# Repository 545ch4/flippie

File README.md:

# flippie

## Basic idea and some background

Usual story: no money, lots of deadlines, unsustainable promises, social responsibility, no time at all, but the unique opportunity to get an additional time-sink. Yeah. Seconds later, I got two huge flip-dot displays I couldn't even carry myself and a lot of single modules. Soon (measured in seasons) it became obvious, that reverse engineering the RS485 based IBIS bus would not make me very happy in the long run. So I decided to throw away the original controller board and drive the flip-dot modules myself. **The goal would be a non intrusive board to directly connect any BROSE display (or array of the same) through the proprietary 60-pin connector...**  So, this is the story of that effort...

### Flip-dot display in general

A flip-dot display consists of a grid of small magnet embedded discs that are black on one side and a bright color on the other (typically white or yellow). The discs are attached to an axle with separate solenoids arranged at the ends or side. By pulsing the solenoid coil with the appropriate electrical polarity, the permanent magnet on the discs align itself with the magnetic field and thus turning (flipping) the disc.

The matrix schematic arranged on a two-dimensional area is shown below.

### BROSE flip-dot

Most BROSE flip-dots are equipped with an [origial FP2800A (or clone)](https://reaktor23.org/_media/projects/flipdot/fp2800-datasheet.pdf) decoder driver as column-selector. It drives one line addressed by 5-bits (A0, A1, A2, B1 and B2) in the direction of D (GND or +VS).  Based on the truth-table, 28 independent column-lines can be driven.

The address lines (ADDR1..ADDR8) are compared to an DIP-switch on each module using a 74HCT688. The output of that comparison drives the ENABLE pin of the FP2800A (through a discrete inverter).

All data and address lines are at 24V logic level. The VS line should be current limited to 350-400 mA, because the coils and/or the FP2800A may blow at higher current.

I did a reverse engineering of the 24V logic at the BROSE display just for illustration. Download as [PDF](https://github.com/545ch4/flippie/raw/master/board/docs/brose_24v_logic.pdf) or [Eagle SCH](https://github.com/545ch4/flippie/raw/master/board/docs/brose_24v_logic.sch).

### BROSE 60-pin connector

## flippie board

The board was designed to drive every serial assembly of modules or single ones non-intrusively - without soldering or modifying the module(s) - simply by connection the proprietary 60-pin BROSE connector. The main MCU [ESP8266](https://espressif.com/en/products/hardware/esp8266ex/overview) is mounted on a USB-interfaced USB-to-Serial converter for convenient programming and WiFi on board. Please see [wemos D1 mini](https://www.wemos.cc/product/d1-mini.html) documentation. Usually you need some driver for the converter to be detected as serial port depending on your OS. The wemos D1 mini comes with a Jiangsu Qinheng CH340/CH341/CH34X or Silicon Labs CP210x chip.

### Block diagram

### Schematics

Since this is my first PCB, the schematic may be slightly unusual. But it works... Suggestions are very welcome. Get the [Eagle SCH file](https://github.com/545ch4/flippie/raw/master/board/flippie.sch) or see the [PDF file](https://github.com/545ch4/flippie/raw/master/board/flippie_schematics.pdf).

### Layout

Download the [Eagle BRD](https://github.com/545ch4/flippie/board/flippie.brd) file and/or the generated [GERBER files as ZIP archive](https://github.com/545ch4/flippie/raw/master/board/gerber.zip). All design rules are taken from [SparkFuns Extended Gerber Format](https://github.com/sparkfun/SparkFun_Eagle_Settings/blob/master/cam/sfe-gerb274x-withGBP.cam).

### BOM

| Part | Value      | Device        | Package       | Description |
|------|------------|---------------|---------------|-------------|
| Part Value | Device | Package | Description |
| C1 | 100uF/50V | CPOL-EU_E | PANASONIC_E | Polarized capacitor, 50V |
| C2 | 10uF/50V | C-EU_C1206 | C1206 | X7R Ceramic Capacitor, 50V |
| C3 | 1uF/50V | C-EU_C1206 | C1206 | X7R Ceramic Capacitor, 50V |
| IC1 | 74HCT245DW | 74HCT245DW | SO20W | Octal BUS TRANSCEIVER, 3-state, TTL/CMOS |
| IC2 | FPF2702MX | FPF2700 | SO8N | AccuPower 0.4~2 A Adjustable Over-Current Protection Load Switch |
| IC3 | SN74AHC595D | SN74AHC595D | SO16N | 8 bit Shift registers |
| ... | ... | ... | ... | ... |
| IC9 | SN74AHC595D | SN74AHC595D | SO16N | 8 bit Shift registers |
| IC10 | TD62783AFG | UDN2981LW | SO18W | PMOS Darlington transistor array |
| IC11 | TD62783AFG | UDN2981LW | SO18W | PMOS Darlington transistor array |
| IC12 | TD62783AFG | UDN2981LW | SO18W | PMOS Darlington transistor array |
| IC13 | ULN2803A | ULN2803ADW | SO18W | NMOS Darlington transistor array |
| ... | ... | ... | ... | ... |
| IC17 | ULN2803A | ULN2803ADW | SO18W | NMOS Darlington transistor array |
| JP1 | 3V3 | JP1E | JP1 | 3.3V Rail Jumper |
| JP2 | 24V | JP1E | JP1 | 24V Rail Jumper |
| JP3 | 5V | JP1E | JP1 | 5V(VCC) Rail Jumper |
| JP4 | VS | JP1E | JP1 | 24V(VS) Jumper |
| LED1 C (red) | LED_SMT1206 | 1206 | LED |
| LED2 B (yellow) | LED_SMT1206 | 1206 | LED |
| LED3 A (green) | LED_SMT1206 | 1206 | LED |
| MCU1 | WEMOS D1 mini | WEMOS D1 mini | WEMOS D1 mini MCU |
| PAD1 (24V) | 2,15/1,0 | 2,15/1,0 | THROUGH-HOLE PAD |
| PAD2 (VS) | 2,15/1,0 | 2,15/1,0 | THROUGH-HOLE PAD |
| R1 | 680K | R-EU_R1206 | R1206 | Current limiter Resistor R_set |
| R2 | 100K | R-EU_R1206 | R1206 | Resistor |
| R3 | 10K | R-EU_R1206 | R1206 | Resistor |
| R4 | 10K | R-EU_R1206 | R1206 | Resistor |
| R5 | 10K | R-EU_R1206 | R1206 | Resistor |
| R6 | 220 | R-EU_R1206 | R1206 | Resistor |
| R7 | 220 | R-EU_R1206 | R1206 | Resistor |
| R8 | 220 | R-EU_R1206 | R1206 | Resistor |
| X1 | 3V3 | JST-XH-02 | JST-XH-02-PACKAGE-LONG-PAD | JST XH Connector 2 Pin |
| X2 | 5V | JST-XH-02 | JST-XH-02-PACKAGE-LONG-PAD | JST XH Connector 2 Pin |
| X3 | 24V | JST-XH-02 | JST-XH-02-PACKAGE-LONG-PAD | JST XH Connector 2 Pin |
| X4 | ~EN_PWR | JST-XH-02 | JST-XH-02-PACKAGE-LONG-PAD | JST XH Connector 2 Pin |
| X5 | BROSE-60-POL | 057-060-1 | 057-060-1 | 60-pol. BROSE CONNECTOR |

### Soldering notes

You can override the whole current limit circuit by shorting/bridging PAD1 (24V) and PAD2 (VS). If you decided to do so, you don't need to populate C1, C2, C3, R1, R2 and IC2.

> **Close JP1 (3V3) and JP2 (24V) but not JP4 (VS) yet.**

## Code

### Prerequisites

Since building and maintaining an ESP8266 toolchain using the [Arduino ESP8266 Framework](https://github.com/ESP8266/Arduino) can be rather frustrating, I decided to use [PlatformIO](http://platformio.org/platformio-ide) with this project.

1. [Download PlatformIO](http://platformio.org/platformio-ide) and install
2. Launch and follow on-screen instructions (install Python-2.7 if necessary)
3. [Install Clang/LLVM](http://docs.platformio.org/en/stable/ide/atom.html#ide-atom-installation-clang)
4. Ensure `platformio-ide` and `platformio-ide-terminal` are enabled (*"Settings > Packages"*)

### Open the project

Download or clone this repository. Open the directory `./code/server` using *"Open project"* at PlatformIO IDE.

### Necessary adoptions

Review you flip-dot addresses: **ADDR8 (8 on the DIP-switch) must be in ON state. We are emulating an overall-enable-pin with that one. Further, the addresses are inverted. So, address 0x01 matches the DIP-switch configuration 1-OFF, 2-ON, ..., 7-ON an 8-ON.**

Before you compile and upload your custom firmware to the ESP8266, there are some values specific to your setup/environment to be defined.
**Flip-dot configuration at `code/server/flippie_device.cpp`:**
```c++
// TODO: How many modules does your display consists of?
const unsigned int num_modules = 4;
config.num_modules = num_modules;
// TODO: What are the addresses (as decimal) of the modules? (see DIP-switches at each module)
config.addresses = new unsigned int[num_modules]{1, 2, 4, 8};
// TODO: How many rows does your display have? (equal over all modules)
config.num_rows = 18;
// TODO: How many columns does each module of your display have? (same order as the addresses)
config.num_columns = new unsigned int[num_modules]{28, 28, 28, 21};
// TODO: Should LED C toggle on each shift-register firing?
config.led_mode = LED_MODE_FLASHING;
```

**WiFi configuration at `code/server/main.cpp`:**
```c++
// TODO: What's the SSID of your WiFi?
const char* ssid = "SSID";
// TODO: What's the PASSWORD of your WiFi?
const char* password = "PASSWORD";
// TODO: If you don't want to use DHCP, provide a static IP (uncomment the following lines). Otherwise leave this commented.
// IPAddress ip(192, 168, 1, 23);
// IPAddress gateway(192, 168, 1, 1);
// IPAddress subnet(255, 255, 255, 0);
// WiFi.config(ip, gateway, subnet);
```

### Compile and upload firmware

> **Please disconnect the power supply of your flippie board or remove the jumper JP1 und JP3 before connecting your computer to the USB port of the ESP8266 (if mounted at the flippie board already).**

Navigate to *"PlatformIO > Build"* to compile this project and create the firmware for uploading to the ESP8266. Use *"PlatformIO > Upload"* to upload your firmware using the USB connection.

### Test

Disconnect flippie from USB or press the reset button of the wemos D1 mini board. Plug the wemos D1 mini to flippie, ensure to close JP1 (3V3), JP2 (24V) and JP3 (5V) **but not JP4 (VS) yet**. All three LEDs should flash three times. If not, the shift-register(s) doesn't seems to work properly... [So, check your soldering.](http://www.infidigm.net/articles/solder/)

If the LEDs were flashing during boot-up, don't yet connect the display itself. Point your browser to `http://<flippie IP>/`. That's the web-interface of flippie. You've done well so far.

Since you don't want to damage your display, we will try to set and reset some dots in a dry run first (**AKA: don't connect your flipdot display yet**):

0. Make sure your display is **not** connected (X5), jumper JP4 (VS) is **closed/shorted** and all three power rails (3V3, 5V and 24V) are enabled through JP1, JP2, JP3.
1. Head to "Low Level" in at flippies web-interface.
2. Fill the form for
   1. Select the address of one of your panels (e.g. 1)
   2. Select a column we are going to use (Column, e.g. 10)
   3. Set "Row SET" to '0' (first row)
   4. Leave "Row RST" undefined
   5. Set the direction D to "1" (D=1 when setting (ROW_SET) and D=0 when reseting (ROW_RST) a pixel)
4. Press "Fire shift-register (PERSISTENT)"
   1. IC12 pin 11 should drive +24V (first row rail, same as pin 1 at X5)
   2. IC16 pin 18 should go to GND (our simulated ENABLE signal, same as pin 60 at X5)
5. Press "Fire shift-register (ENABLE)" to quit "PERSISTENT" mode.

Repeat the test with flipdot display connected (X5):

0. Make sure your display **is** connected (X5), jumper JP4 (VS) is **open** and all three power rails (3V3, 5V and 24V) are enabled through JP1, JP2, JP3.
1. Head to "Low Level" in at flippies web-interface.
2. Fill the form for
   1. Select the address of one of your panels (e.g. 1)
   2. Select a column we are going to use (Column, e.g. 10)
   3. Set "Row SET" to '0' (first row)
   4. Leave "Row RST" undefined
   5. Set the direction D to "1" (D=1 when setting (ROW_SET) and D=0 when reseting (ROW_RST) a pixel)
4. Press "Fire shift-register (PERSISTENT)"
5. Now take a jumper and use it to **shortly bypass** (close shortly and then open again) JP4 (VS): **The dot should flip!**
6. Repeat the procedure with "Row SET" undefined, "Row RST" set to '0' and D set to '0'. **The dot should flip back!**
5. Press "Fire shift-register (ENABLE)" to quit "PERSISTENT" mode.

**Well done!** You're ready to use your flippie! [Simply head over to "Paint" and draw something.](#paint)

### Firmware API documentation

Flippie is basically a simple web server at port 80 serving the following access points:

**`/ui` – UI pages**  
A simple index page with browser UI controlling the flip-dot. All javascript and stylesheets are loaded from an external CDN, not from the ESP8266 itself. So, you need to be connected to the internet... (Yes, it's an TODO.)

The UI does have a nice drawing pane, where every pixel can be set/reset like painting using a HTML5 canvas.

**`/dots` – A receiver of base64 encoded dots vector**  
This method reads the content of HTTP (POST/GET) variable `dots` which is a base64 encoded string. This string is build of 32-bit wide integers (four bytes) where each bit (0-31) represents the state of one column. Those integers are ordered by rows and then modules:
```
[row 1 column 1-32* module 1], [row 1 column 1-32* module 2], ..., [row 1 column 1-32* module M], [row 2 column 1-32* module 1], [row 2 column 1-32* module 2], ..., ..., [row R column 1-32* module M]
```
\* max, could be less, ignoring unnecessary bits. Each integer is packed as four 8-bit characters in LSB order.

**`/flippie` – Directly alter the shift register at flippie (possibly dangerous)**

Low level access to flippie. Set using HTTP variables (POST) and retrieve values as JSON using GET. POST request will return JSON `true`.

| HTTP verb | Variable       | Value           | Description                   |
|-----------|----------------|---------------- |-------------------------------|
| GET/POST  | led_X          | 0, 1            | Get/Set the state of LED X (A, B, C) |
| GET/POST  | address        | 0 - 127         | Get/Set the module address |
| GET/POST  | column         | 0 - 27          | Get/Set the active column |
| GET/POST  | d              | 0, 1            | Set FP2800A D pin (1 = selected column set to GND, 0 = selected column set to +VS) |
| GET/POST  | row_set        | 0 - 19          | Set the selected row to +VS |
| GET/POST  | row_rst        | 0 - 19          | Set the selected row to GND |
| GET/POST  | enable         | 0, 1            | Set enable if 1 (dangerous) |
| POST      | clear          | 0, 1            | Clear shift-register if 1 |
| GET       | shiftregister  | String          | Get contents of the shift-register as sequence of zeros and ones. |
| POST      | task           | clear           | Clear the whole display |
| POST      | task           | fill            | Fill the whole display (set all dots) |
| POST      | task           | inverse         | Inverse the whole display |
| POST      | task           | magnetize       | Magnetize the whole display |

Basic mechanism to set a dot (column 2, row 3) at module 0 with address 0x01 (DIP switch 0-1-1-1-1-1-1-0) using raw HTTP:
```shell
$ telnet <flippie IP> 80
> POST /flippie HTTP/1.0
> Content-Length: 41
>
> address=1&column=1&row_set=2&d=1&enable=1
```

**`/pixel` – Set individual pixels**

| HTTP Variable          | Description |
|------------------------|-------------|
| r(0-31)                | Row |
| m(0-128)               | Module |
| c(0-31)                | Column |
| state(0/1)             | Set of reset the pixel |

A GET request will reveal the state of an pixel and a POST will set the state.

## Demo ruby client

There's a simple demo-like ruby implementation to write text at a given display. To use it, please head yourself to the directory `./client/` and initialize the ruby environment with:
```shell
gem install bundler
bundle install
```

Adjust flippies credentials in `cli.rb`:
```ruby
# initialize new flippie client
fc = FlippieClient.new(
   '192.168.1.23',     # IP address of your flippie board
   18,                  # number of rows of your flip-dot display
   [21],                # number of columns per module (usually some 28ers an one 21er)
   false                # debug => true
)
```

You are now ready to send messages/text to your flippie board using the ruby tool. Example:
```shell
./cli.rb YES
```
You should see an visual response of "YES" on your command line as well as the same text on your flip-dot display, obviously. See the source for further options.

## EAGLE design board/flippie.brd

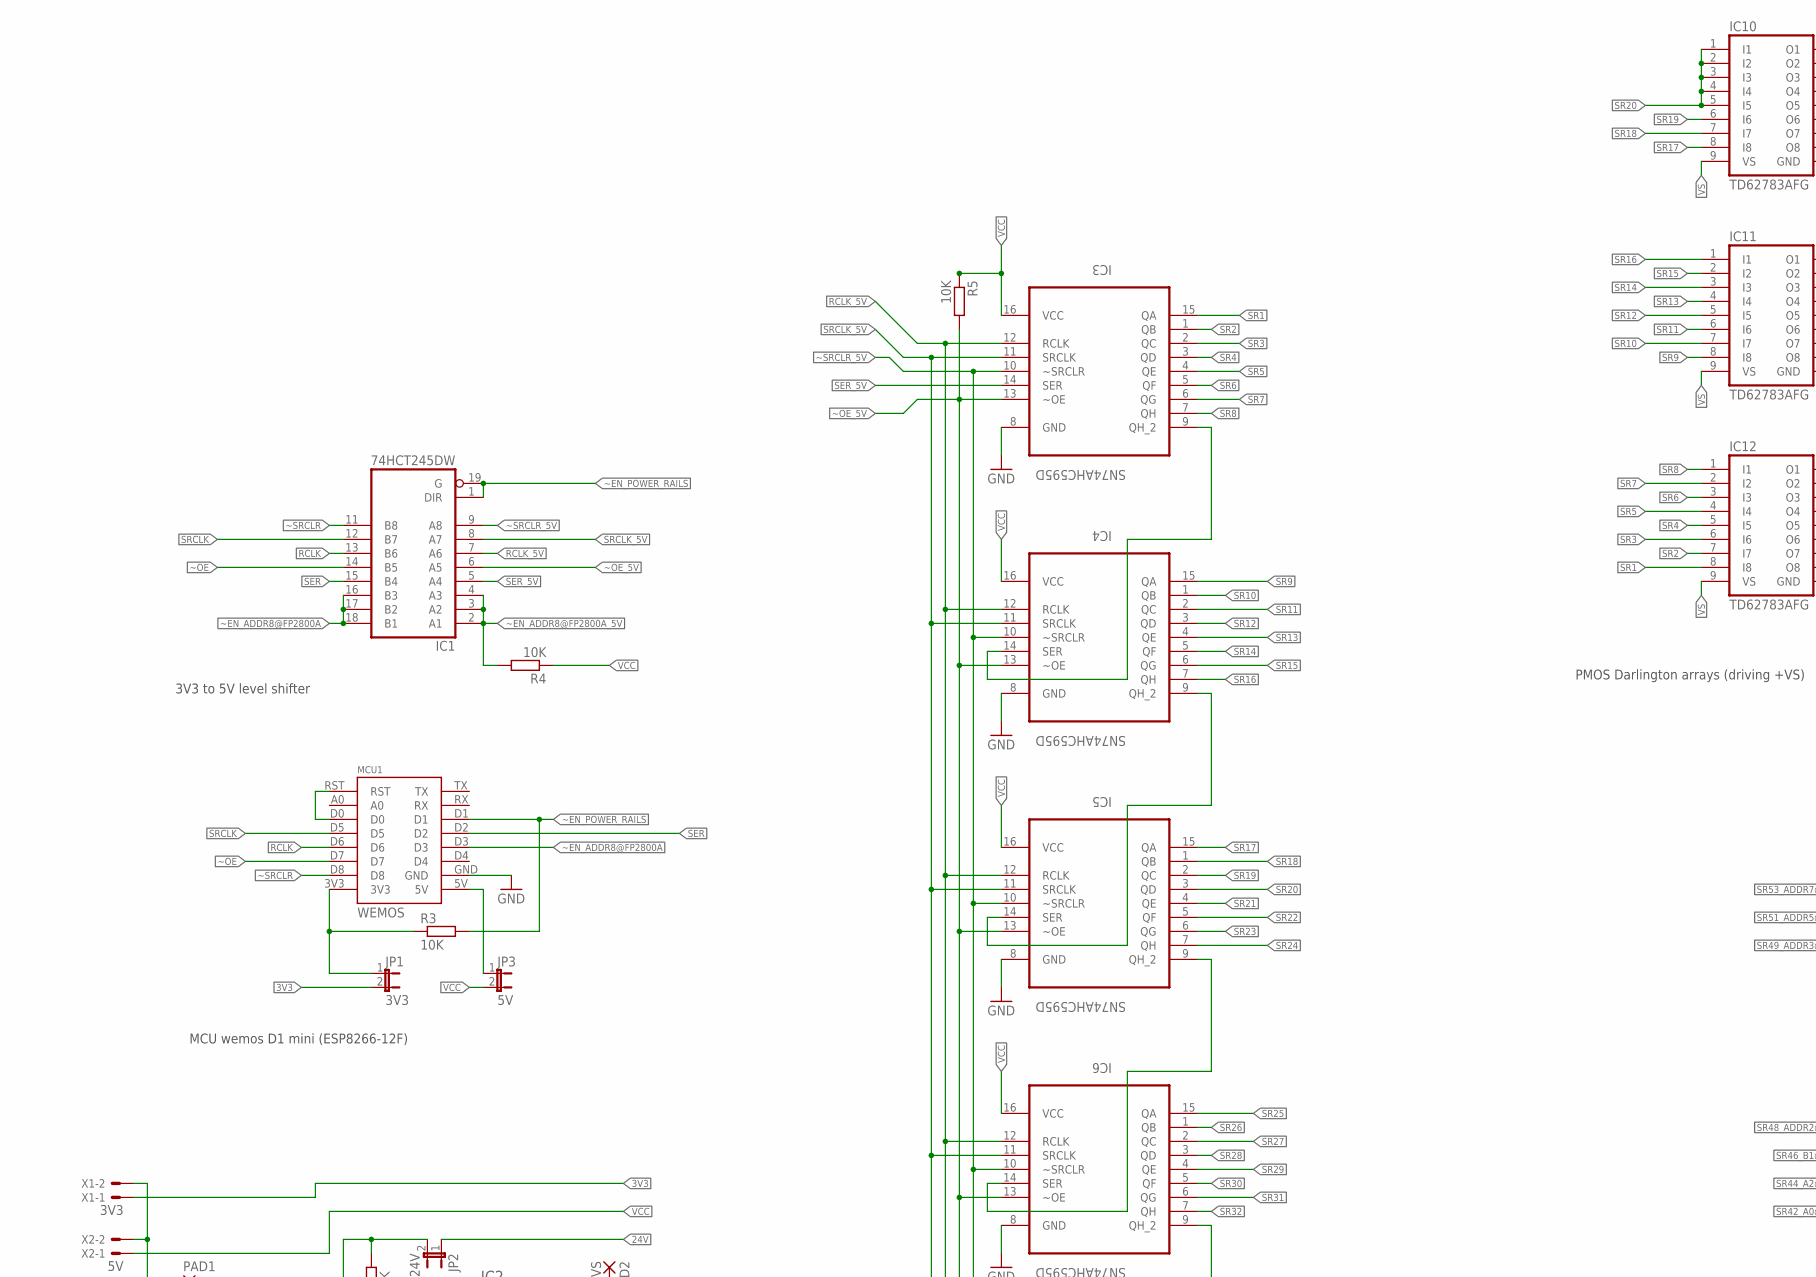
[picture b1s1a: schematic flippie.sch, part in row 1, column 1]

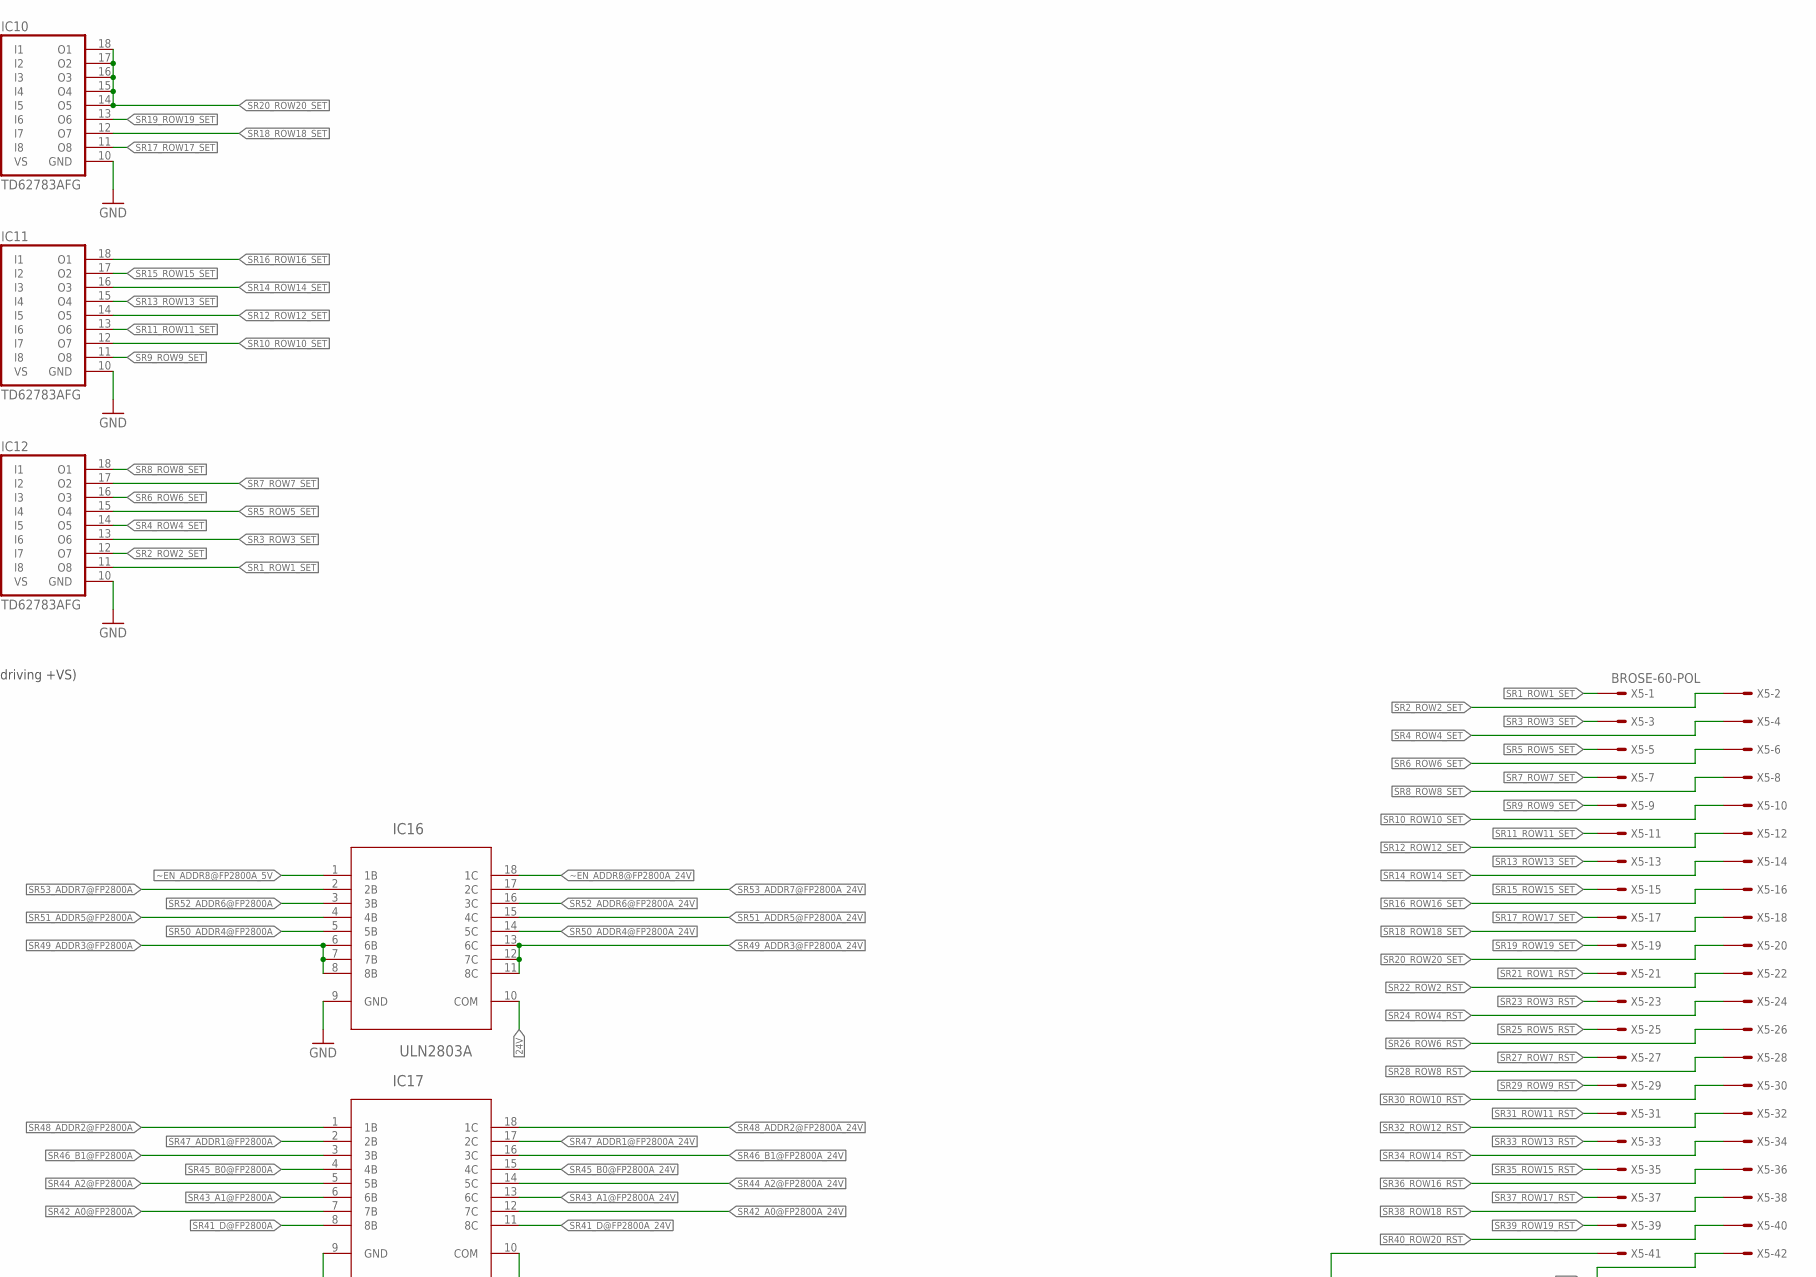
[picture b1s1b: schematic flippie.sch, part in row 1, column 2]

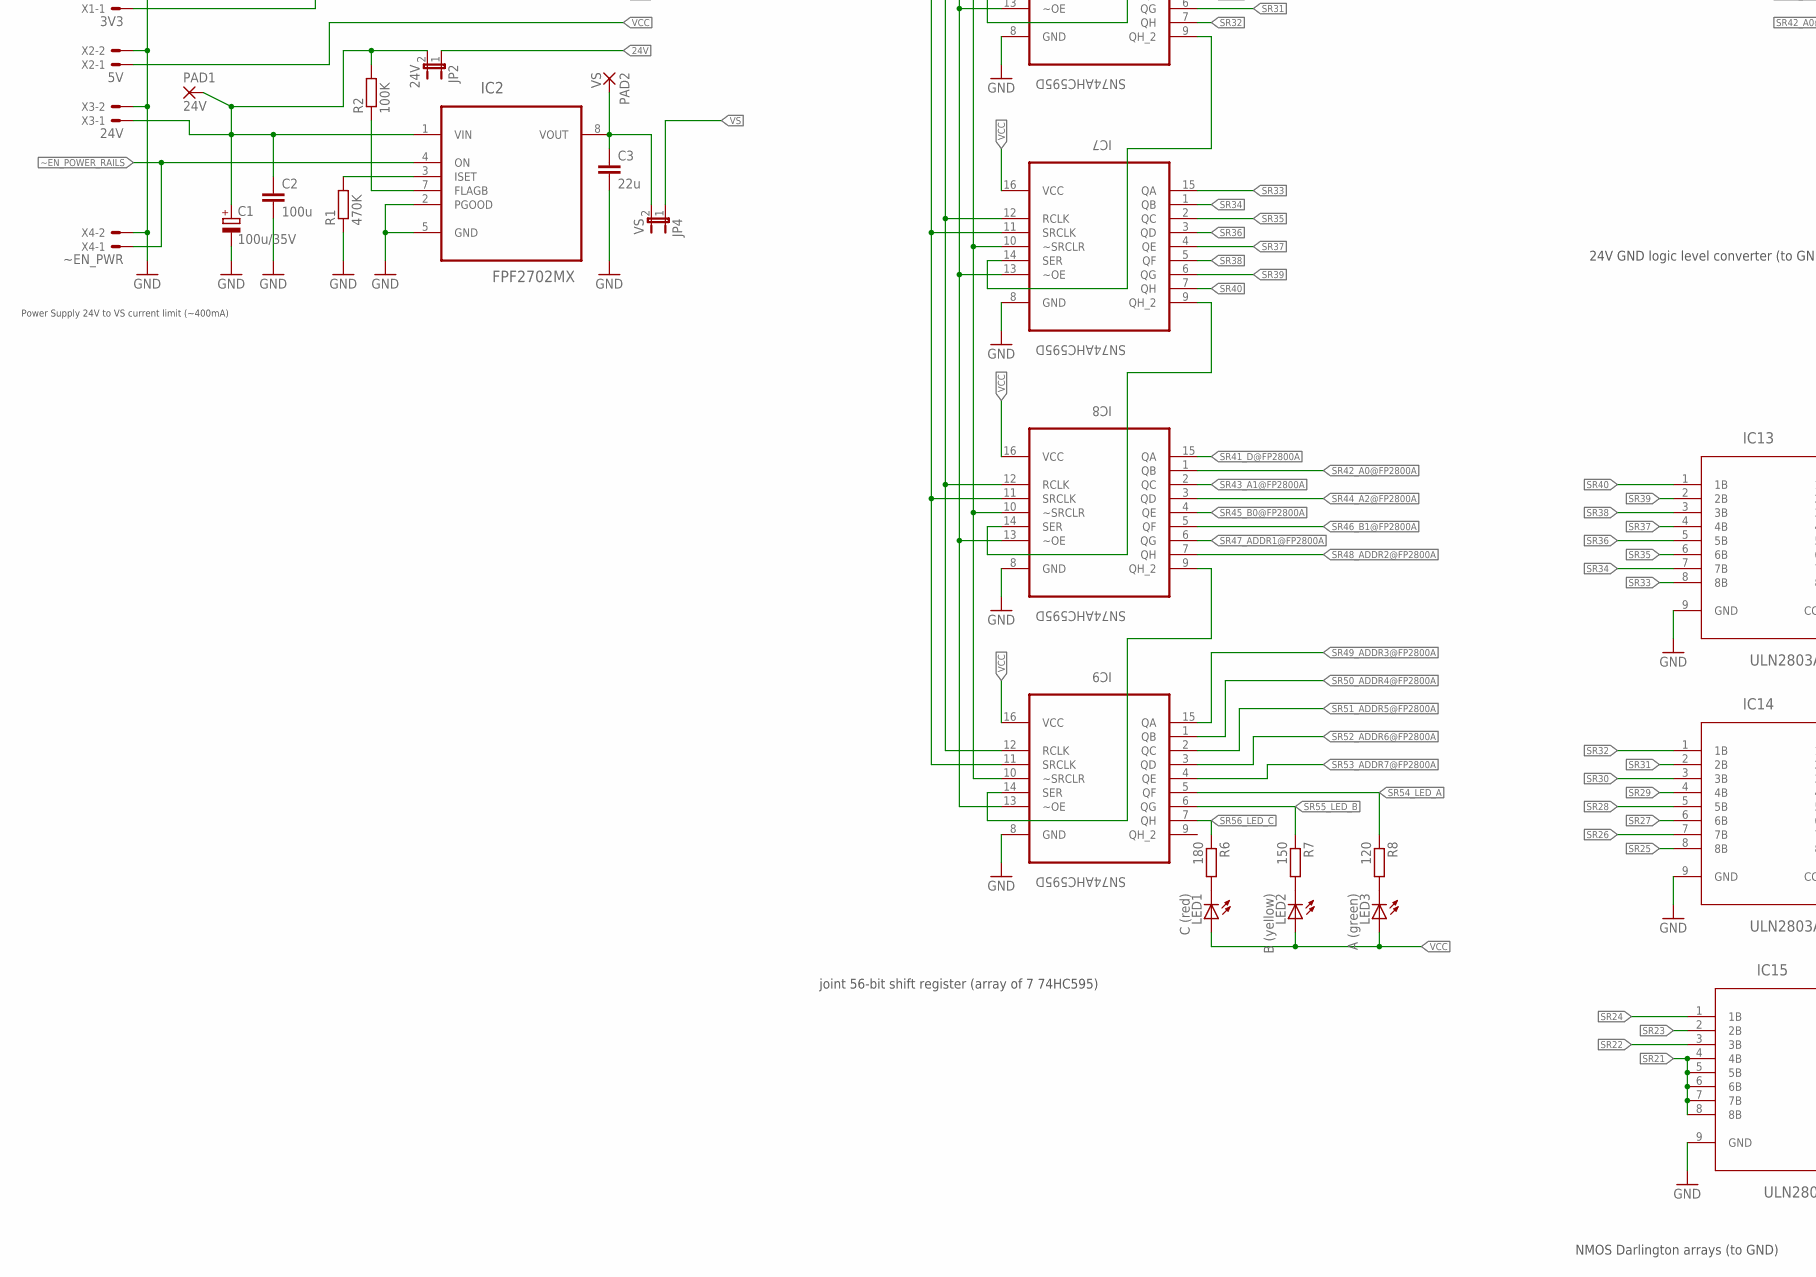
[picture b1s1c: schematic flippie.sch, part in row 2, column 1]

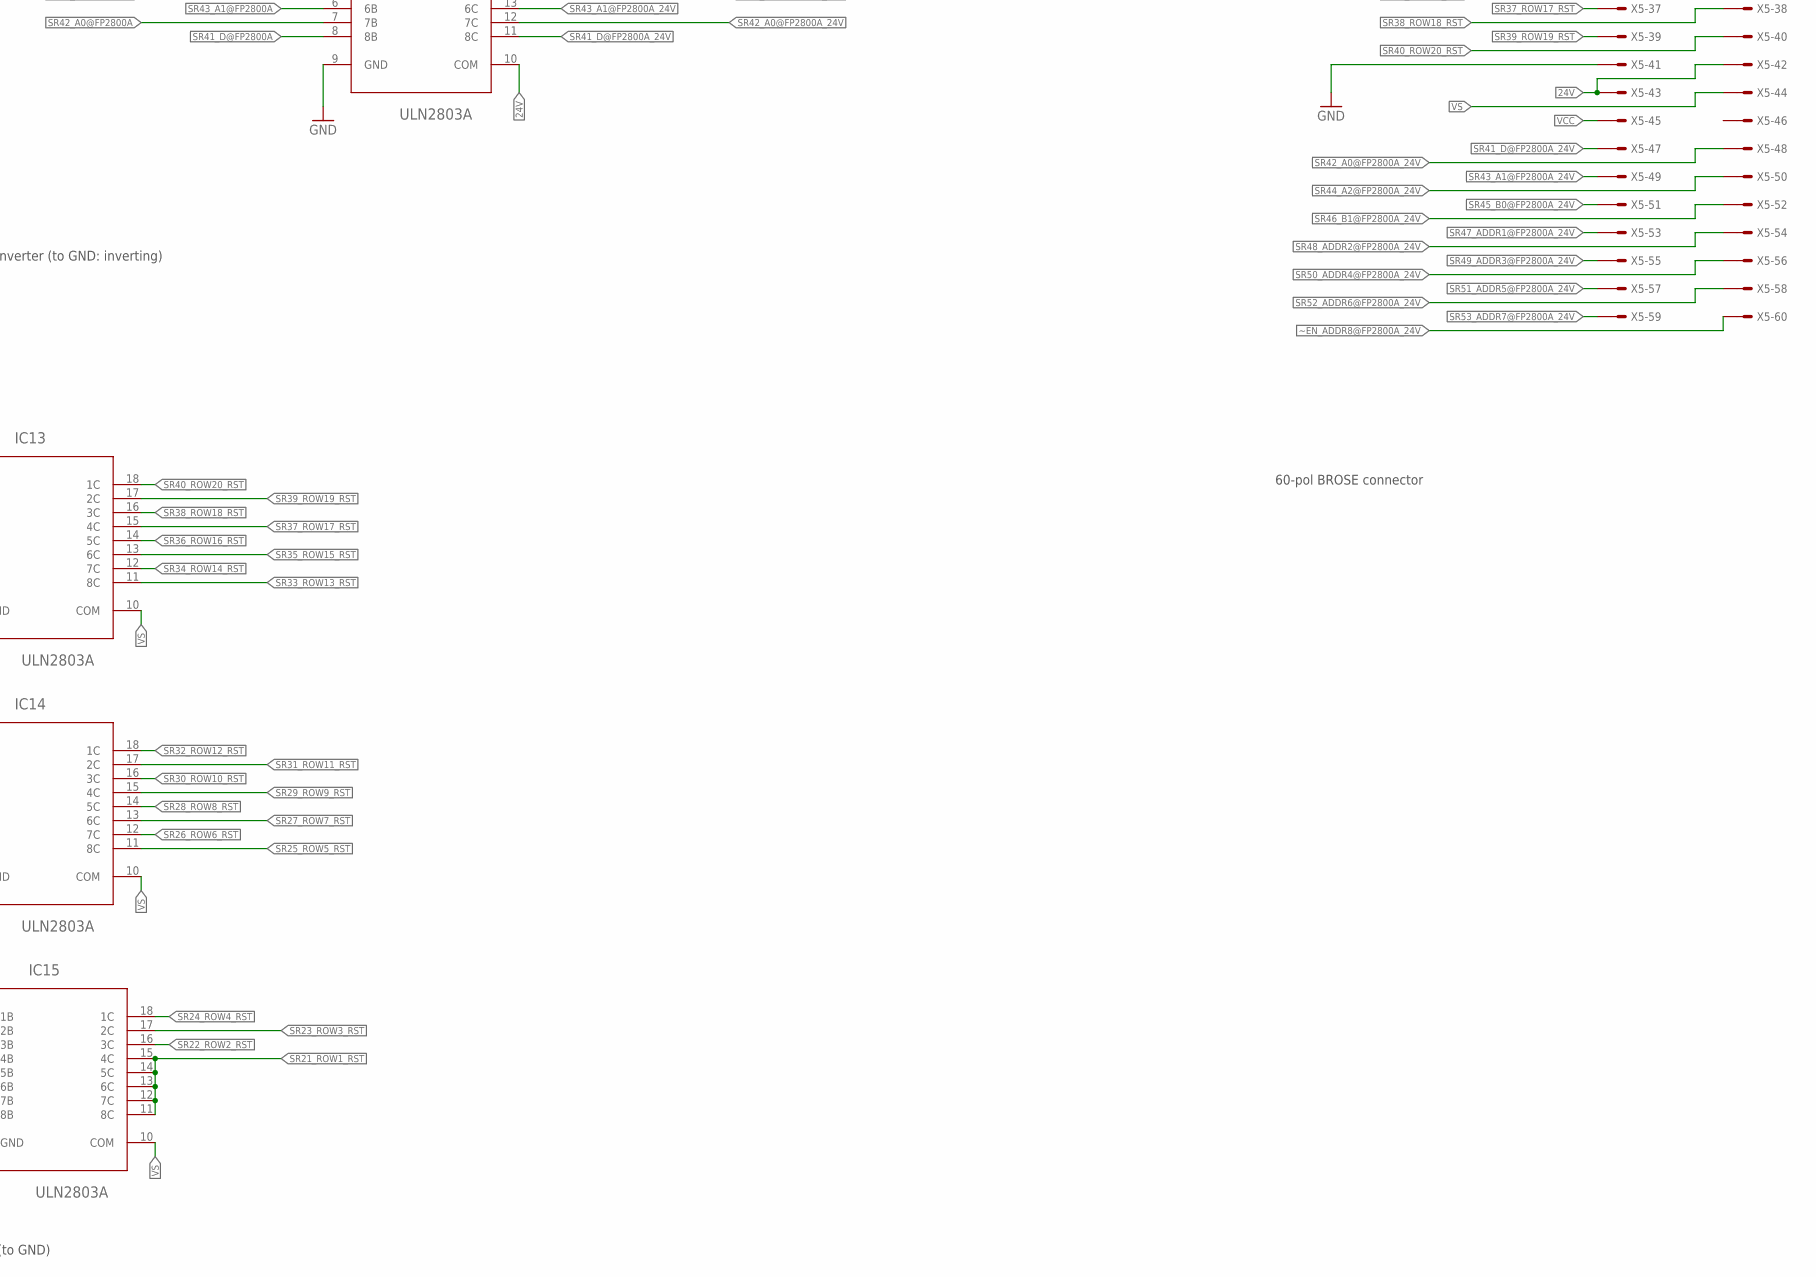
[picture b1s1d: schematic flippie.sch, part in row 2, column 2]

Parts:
C1: 100u/35V; PANASONIC_E
C2: 100u; C1206
C3: 22u; C1206
IC1: 74HCT245DW; SO20W
IC2: FPF2702MX; SOIC127P600X175-8N
IC3, IC4, IC5, IC6, IC7, IC8, IC9: SN74AHC595D; SOIC127P600X175-16N
IC10, IC11, IC12: TD62783AFG; SO18W
IC13, IC14, IC15, IC16, IC17: ULN2803A; SOIC127P1030X265-18N
JP1: 3V3; JP1
JP2: 24V; JP1
JP3: 5V; JP1
JP4: VS; JP1
LED1: C (red); 1206
LED2: B (yellow); 1206
LED3: A (green); 1206
MCU1: WEMOS
PAD1: 24V; 2,15/1,0
PAD2: VS; 2,15/1,0
R1: 470K; R1206
R2: 100K; R1206
R3, R4, R5: 10K; R1206
R6: 180; R1206
R7: 150; R1206
R8: 120; R1206
X1: 3V3; JST-XH-02-PACKAGE-LONG-PAD
X2: 5V; JST-XH-02-PACKAGE-LONG-PAD
X3: 24V; JST-XH-02-PACKAGE-LONG-PAD
X4: ~EN_PWR; JST-XH-02-PACKAGE-LONG-PAD
X5: BROSE-60-POL; 057-060-1

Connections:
3V3: JP1.2, X1.1
3V3_SW: JP1.1, MCU1.3V3, R3.1
24V: IC16.10 (COM), IC17.10 (COM), JP2.1, X5.42, X5.43
24V_SW: C1.+, C2.1, IC2.1 (VIN), JP2.2, PAD1.1, R2.2, X3.1
GND: C1.-, C2.2, C3.2, IC1.10 (GND), IC2.2 (PGOOD), IC2.5 (GND), IC3.8 (GND), IC4.8 (GND), IC5.8 (GND), IC6.8 (GND), IC7.8 (GND), IC8.8 (GND), IC9.8 (GND), IC10.10 (GND), IC11.10 (GND), IC12.10 (GND), IC13.9 (GND), IC14.9 (GND), IC15.9 (GND), IC16.9 (GND), IC17.9 (GND), MCU1.GND, R1.1, X1.2, X2.2, X3.2, X4.2, X5.41
unnamed: IC6.9 (QH_2), IC7.14 (SER)
unnamed: IC2.7 (FLAGB), R2.1
unnamed: IC2.3 (ISET), R1.2
unnamed: LED1.C, R6.2
unnamed: IC8.9 (QH_2), IC9.14 (SER)
unnamed: MCU1.D0, MCU1.RST
unnamed: IC4.9 (QH_2), IC5.14 (SER)
unnamed: LED2.C, R7.2
unnamed: IC5.9 (QH_2), IC6.14 (SER)
unnamed: LED3.C, R8.2
unnamed: IC3.9 (QH_2), IC4.14 (SER)
unnamed: IC7.9 (QH_2), IC8.14 (SER)
RCLK: IC1.13 (B6), MCU1.D6
RCLK_5V: IC1.7 (A6), IC3.12 (RCLK), IC4.12 (RCLK), IC5.12 (RCLK), IC6.12 (RCLK), IC7.12 (RCLK), IC8.12 (RCLK), IC9.12 (RCLK)
SER: IC1.15 (B4), MCU1.D2
SER_5V: IC1.5 (A4), IC3.14 (SER)
SR1: IC3.15 (QA), IC12.8 (I8)
SR1_ROW1_SET: IC12.11 (O8), X5.1
SR2: IC3.1 (QB), IC12.7 (I7)
SR2_ROW2_SET: IC12.12 (O7), X5.2
SR3: IC3.2 (QC), IC12.6 (I6)
SR3_ROW3_SET: IC12.13 (O6), X5.3
SR4: IC3.3 (QD), IC12.5 (I5)
SR4_ROW4_SET: IC12.14 (O5), X5.4
SR5: IC3.4 (QE), IC12.4 (I4)
SR5_ROW5_SET: IC12.15 (O4), X5.5
SR6: IC3.5 (QF), IC12.3 (I3)
SR6_ROW6_SET: IC12.16 (O3), X5.6
SR7: IC3.6 (QG), IC12.2 (I2)
SR7_ROW7_SET: IC12.17 (O2), X5.7
SR8: IC3.7 (QH), IC12.1 (I1)
SR8_ROW8_SET: IC12.18 (O1), X5.8
SR9: IC4.15 (QA), IC11.8 (I8)
SR9_ROW9_SET: IC11.11 (O8), X5.9
SR10: IC4.1 (QB), IC11.7 (I7)
SR10_ROW10_SET: IC11.12 (O7), X5.10
SR11: IC4.2 (QC), IC11.6 (I6)
SR11_ROW11_SET: IC11.13 (O6), X5.11
SR12: IC4.3 (QD), IC11.5 (I5)
SR12_ROW12_SET: IC11.14 (O5), X5.12
SR13: IC4.4 (QE), IC11.4 (I4)
SR13_ROW13_SET: IC11.15 (O4), X5.13
SR14: IC4.5 (QF), IC11.3 (I3)
SR14_ROW14_SET: IC11.16 (O3), X5.14
SR15: IC4.6 (QG), IC11.2 (I2)
SR15_ROW15_SET: IC11.17 (O2), X5.15
SR16: IC4.7 (QH), IC11.1 (I1)
SR16_ROW16_SET: IC11.18 (O1), X5.16
SR17: IC5.15 (QA), IC10.8 (I8)
SR17_ROW17_SET: IC10.11 (O8), X5.17
SR18: IC5.1 (QB), IC10.7 (I7)
SR18_ROW18_SET: IC10.12 (O7), X5.18
SR19: IC5.2 (QC), IC10.6 (I6)
SR19_ROW19_SET: IC10.13 (O6), X5.19
SR20: IC5.3 (QD), IC10.1 (I1), IC10.2 (I2), IC10.3 (I3), IC10.4 (I4), IC10.5 (I5)
SR20_ROW20_SET: IC10.14 (O5), IC10.15 (O4), IC10.16 (O3), IC10.17 (O2), IC10.18 (O1), X5.20
SR21: IC5.4 (QE), IC15.4 (4B), IC15.5 (5B), IC15.6 (6B), IC15.7 (7B), IC15.8 (8B)
SR21_ROW1_RST: IC15.11 (8C), IC15.12 (7C), IC15.13 (6C), IC15.14 (5C), IC15.15 (4C), X5.21
SR22: IC5.5 (QF), IC15.3 (3B)
SR22_ROW2_RST: IC15.16 (3C), X5.22
SR23: IC5.6 (QG), IC15.2 (2B)
SR23_ROW3_RST: IC15.17 (2C), X5.23
SR24: IC5.7 (QH), IC15.1 (1B)
SR24_ROW4_RST: IC15.18 (1C), X5.24
SR25: IC6.15 (QA), IC14.8 (8B)
SR25_ROW5_RST: IC14.11 (8C), X5.25
SR26: IC6.1 (QB), IC14.7 (7B)
SR26_ROW6_RST: IC14.12 (7C), X5.26
SR27: IC6.2 (QC), IC14.6 (6B)
SR27_ROW7_RST: IC14.13 (6C), X5.27
SR28: IC6.3 (QD), IC14.5 (5B)
SR28_ROW8_RST: IC14.14 (5C), X5.28
SR29: IC6.4 (QE), IC14.4 (4B)
SR29_ROW9_RST: IC14.15 (4C), X5.29
SR30: IC6.5 (QF), IC14.3 (3B)
SR30_ROW10_RST: IC14.16 (3C), X5.30
SR31: IC6.6 (QG), IC14.2 (2B)
SR31_ROW11_RST: IC14.17 (2C), X5.31
SR32: IC6.7 (QH), IC14.1 (1B)
SR32_ROW12_RST: IC14.18 (1C), X5.32
SR33: IC7.15 (QA), IC13.8 (8B)
SR33_ROW13_RST: IC13.11 (8C), X5.33
SR34: IC7.1 (QB), IC13.7 (7B)
SR34_ROW14_RST: IC13.12 (7C), X5.34
SR35: IC7.2 (QC), IC13.6 (6B)
SR35_ROW15_RST: IC13.13 (6C), X5.35
SR36: IC7.3 (QD), IC13.5 (5B)
SR36_ROW16_RST: IC13.14 (5C), X5.36
SR37: IC7.4 (QE), IC13.4 (4B)
SR37_ROW17_RST: IC13.15 (4C), X5.37
SR38: IC7.5 (QF), IC13.3 (3B)
SR38_ROW18_RST: IC13.16 (3C), X5.38
SR39: IC7.6 (QG), IC13.2 (2B)
SR39_ROW19_RST: IC13.17 (2C), X5.39
SR40: IC7.7 (QH), IC13.1 (1B)
SR40_ROW20_RST: IC13.18 (1C), X5.40
SR41_D@FP2800A: IC8.15 (QA), IC17.8 (8B)
SR41_D@FP2800A_24V: IC17.11 (8C), X5.47
SR42_A0@FP2800A: IC8.1 (QB), IC17.7 (7B)
SR42_A0@FP2800A_24V: IC17.12 (7C), X5.48
SR43_A1@FP2800A: IC8.2 (QC), IC17.6 (6B)
SR43_A1@FP2800A_24V: IC17.13 (6C), X5.49
SR44_A2@FP2800A: IC8.3 (QD), IC17.5 (5B)
SR44_A2@FP2800A_24V: IC17.14 (5C), X5.50
SR45_B0@FP2800A: IC8.4 (QE), IC17.4 (4B)
SR45_B0@FP2800A_24V: IC17.15 (4C), X5.51
SR46_B1@FP2800A: IC8.5 (QF), IC17.3 (3B)
SR46_B1@FP2800A_24V: IC17.16 (3C), X5.52
SR47_ADDR1@FP2800A: IC8.6 (QG), IC17.2 (2B)
SR47_ADDR1@FP2800A_24V: IC17.17 (2C), X5.53
SR48_ADDR2@FP2800A: IC8.7 (QH), IC17.1 (1B)
SR48_ADDR2@FP2800A_24V: IC17.18 (1C), X5.54
SR49_ADDR3@FP2800A: IC9.15 (QA), IC16.6 (6B), IC16.7 (7B), IC16.8 (8B)
SR49_ADDR3@FP2800A_24V: IC16.11 (8C), IC16.12 (7C), IC16.13 (6C), X5.55
SR50_ADDR4@FP2800A: IC9.1 (QB), IC16.5 (5B)
SR50_ADDR4@FP2800A_24V: IC16.14 (5C), X5.56
SR51_ADDR5@FP2800A: IC9.2 (QC), IC16.4 (4B)
SR51_ADDR5@FP2800A_24V: IC16.15 (4C), X5.57
SR52_ADDR6@FP2800A: IC9.3 (QD), IC16.3 (3B)
SR52_ADDR6@FP2800A_24V: IC16.16 (3C), X5.58
SR53_ADDR7@FP2800A: IC9.4 (QE), IC16.2 (2B)
SR53_ADDR7@FP2800A_24V: IC16.17 (2C), X5.59
SR54_LED_A: IC9.5 (QF), R8.1
SR55_LED_B: IC9.6 (QG), R7.1
SR56_LED_C: IC9.7 (QH), R6.1
SRCLK: IC1.12 (B7), MCU1.D5
SRCLK_5V: IC1.8 (A7), IC3.11 (SRCLK), IC4.11 (SRCLK), IC5.11 (SRCLK), IC6.11 (SRCLK), IC7.11 (SRCLK), IC8.11 (SRCLK), IC9.11 (SRCLK)
VCC: IC1.20 (VCC), IC3.16 (VCC), IC4.16 (VCC), IC5.16 (VCC), IC6.16 (VCC), IC7.16 (VCC), IC8.16 (VCC), IC9.16 (VCC), JP3.2, LED1.A, LED2.A, LED3.A, R4.1, R5.1, X2.1, X5.45
VCC_SW: JP3.1, MCU1.5V
VS: IC10.9 (VS), IC11.9 (VS), IC12.9 (VS), IC13.10 (COM), IC14.10 (COM), IC15.10 (COM), JP4.1, X5.44
VS_SW: C3.1, IC2.8 (VOUT), JP4.2, PAD2.1
~EN_ADDR8@FP2800A: IC1.16 (B3), IC1.17 (B2), IC1.18 (B1), MCU1.D3
~EN_ADDR8@FP2800A_5V: IC1.2 (A1), IC1.3 (A2), IC1.4 (A3), IC16.1 (1B), R4.2
~EN_ADDR8@FP2800A_24V: IC16.18 (1C), X5.60
~EN_POWER_RAILS: IC1.1 (DIR), IC1.19 (G), IC2.4 (ON), MCU1.D1, R3.2, X4.1
~OE: IC1.14 (B5), MCU1.D7
~OE_5V: IC1.6 (A5), IC3.13 (~OE), IC4.13 (~OE), IC5.13 (~OE), IC6.13 (~OE), IC7.13 (~OE), IC8.13 (~OE), IC9.13 (~OE), R5.2
~SRCLR: IC1.11 (B8), MCU1.D8
~SRCLR_5V: IC1.9 (A8), IC3.10 (~SRCLR), IC4.10 (~SRCLR), IC5.10 (~SRCLR), IC6.10 (~SRCLR), IC7.10 (~SRCLR), IC8.10 (~SRCLR), IC9.10 (~SRCLR)

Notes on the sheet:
MCU wemos D1 mini (ESP8266-12F)
joint 56-bit shift register (array of 7 74HC595)
PMOS Darlington arrays (driving +VS)
NMOS Darlington arrays (to GND)
60-pol BROSE connector
Power Supply 24V to VS current limit (~400mA)
24V GND logic level converter (to GND: inverting)
3V3 to 5V level shifter

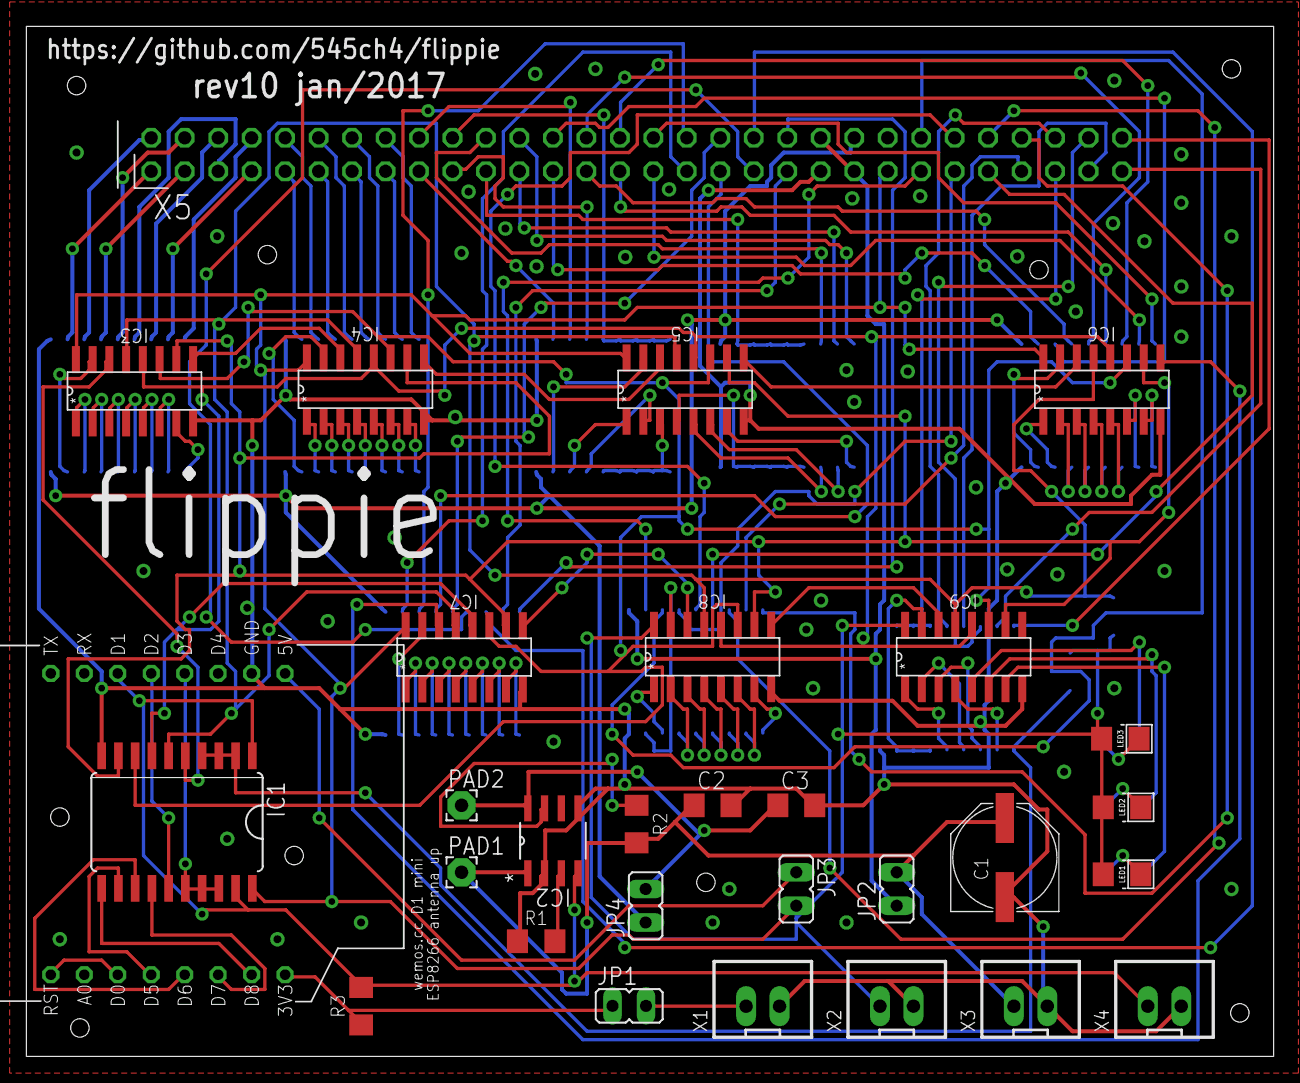
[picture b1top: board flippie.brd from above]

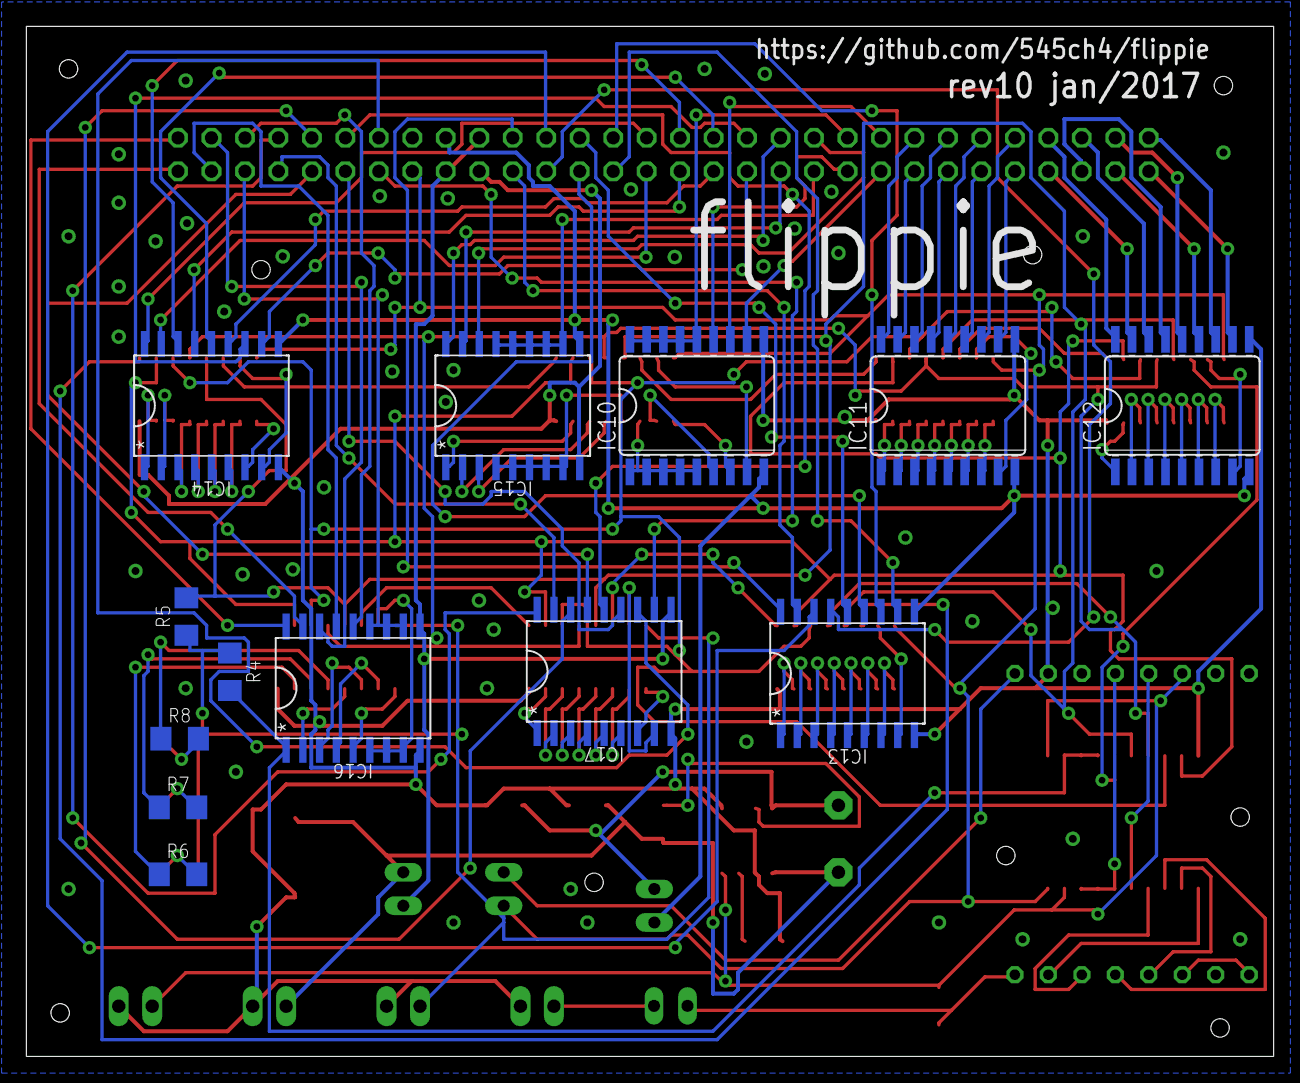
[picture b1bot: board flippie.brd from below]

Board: 2 copper layers, 94.6 x 78.2 mm, 43 parts (13 on the bottom side), 144 nets.

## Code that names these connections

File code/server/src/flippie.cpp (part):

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  config->sr_led_c_pin = 55;

  // shift-register input
  // 74*595 shift-register clear pin [normal:high, clear:low] (~MR, ~SRCLR,
  // ~SCLR, ~SCL)
  config->not_clear_pin = D8;
  // 74*595 shift-register clock pin (SH_CP, SRCLK, SCK)
  config->clock_pin = D5;
  // 74*595 shift-register storage register clock pin (latch) (ST_CP, RCLK, RCK)
  config->latch_pin = D6;
  // 74*595 shift-register output enable pin [normal:low, tristate output:high]
  // (~G, ~OE)
  config->not_output_enable_pin = D7;
  // 74*595 shift-register serial data input pin (DS, SER, A, SI)
  config->serial_data_pin = D2;

  // ~EN_POWER_RAILS pin (eg. ON pin at current limiter FPF2702MX circuit)
  config->not_enable_power_rails_pin = D1;

  // ~EN and ADDR8@FP2800A
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
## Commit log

2016-11-05 Added BOM
2016-11-05 Minior fixes
2016-11-07 Some clean-ups
2016-11-07 Updated BOM
2016-11-08 Updated server sources
2016-11-09 Updated client sources
2016-11-09 Start writing README documentation
2016-11-10 Updated server
2016-11-10 Continue to write README documentation
2016-12-28 Update board to rev10
2017-01-13 Reduced set/reset time
2017-01-13 Corrected R_set value for less current at VS
2017-01-13 Corrected typos and README text
2019-08-24 Fix PROGMEM issue
